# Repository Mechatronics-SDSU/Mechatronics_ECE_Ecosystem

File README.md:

# Mechatronics_ECE_Ecosystem
Center for anything that makes lights blink and motors spin.
  
The new revision of a cohesive electrical system to support all Mechatronics projects consisting of several "modules" communicating on shared multi-drop buses. 
Each module consists of:
- Hardware (schematic + PCB)
- Firmware and Build Files
- Fabrication files
  
Each module shall:
- Have a specific and well scoped goal
- Serve to more efficiently distribute processing as a part of the whole system
- Respect the shared communications standards defined in this repository
- Be well researched, tested, and documented

## Repository Structure
- Embedded CAN Bus
    - Contains documentation and libraries for inter-module communications

- Board Support
    - List of supported hardware
    - Contains information on supported MCU/FPGAs
    - Example projects and guides on how to use and implement a specific device

- General Documentation
    - well... it's in the name
    - Overall architectural goals and descriptions of our target system and all current/future needs

- KiCad Libraries
    - KiCad 7 symbols, footprints, and models created for individual modules

## General Hardware Support
A set of selected processors and FPGAs are listed that contain the requisite information to quickly bring any project up. These parts are by no means the only acceptable options, but are provided to reduce the load when starting a project.

Also run linux, it makes all of this so much easier. :)

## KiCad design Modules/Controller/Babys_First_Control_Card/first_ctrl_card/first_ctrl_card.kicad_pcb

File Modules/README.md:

# Modules
Several modules are required to sustain an effective system.  
A module may be standalone, or represent a subsystem that requires a single point of bus interface (notably Power System Management).
  
To better organize the multiple projects that will be present here another layer of directories are present.
### Acoustics and Communication
- Hydrophone direction finding
- Acoustic data processing / collection
- Optical and Acoustic Communications methods
### Controller
- Main bus controller
- Interface with embedded computers (Jetsons, Pis, etc..)
### Human Interface
- Controls boxes
- Lighting systems
### Motion
- ESC Drivers
- Servo Controllers
- Motion Processing
### Power Systm
- Power conversion (DC-DC, AC-DC)
- Power monitoring
- Battery priority and failover
- Battery charging
- Power path management
### Safety
- Internal system state
- Temperature and leak monitoring
- General system watchdog
### Example
- Template Project

## Completed Modules
  
## Modules In Progress
- Bus Manager / Computer Interface Module
- Human Interface Module
- System Health Monitoring Module
- Motor and Drive Control Module
- RGB Pattern Module
- Power System Management
- Hydrophone Direction Finding
- Acoustic Communications
- A ton of power projects

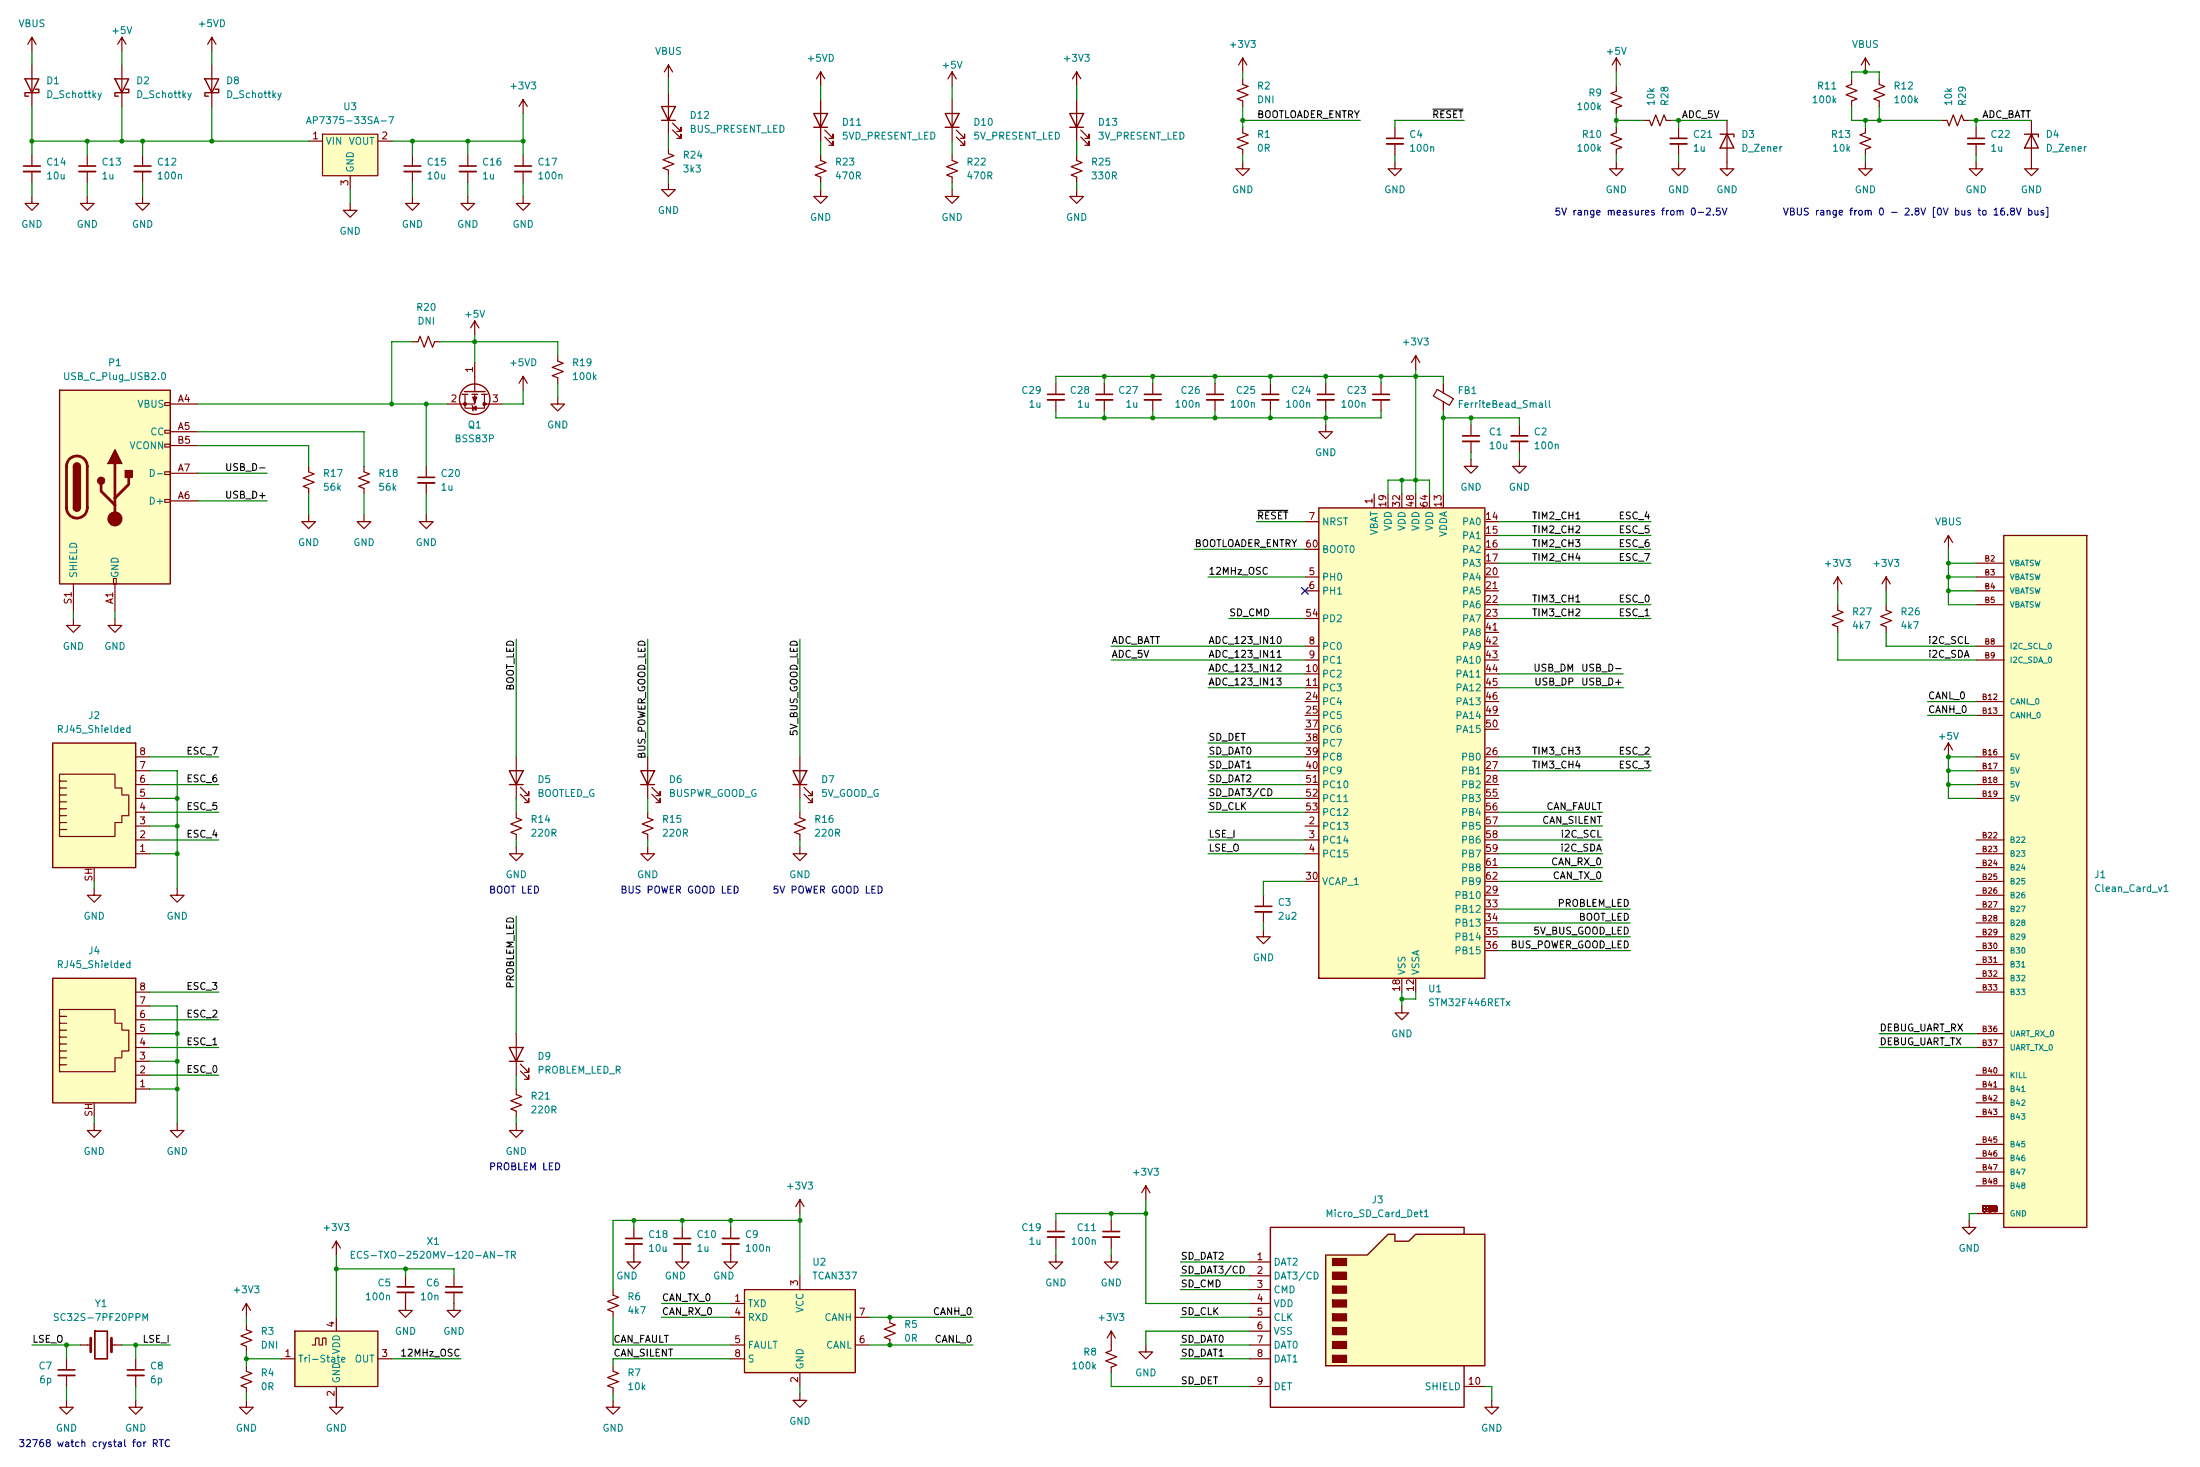
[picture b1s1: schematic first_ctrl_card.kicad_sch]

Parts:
C1, C14, C15, C18: 10u; C_0805_2012Metric
C2, C4, C5, C9, C11, C12, C17, C23, C24, C25, C26: 100n; C_0805_2012Metric
C3: 2u2; C_0805_2012Metric
C6: 10n; C_0805_2012Metric
C7, C8: 6p; C_0805_2012Metric
C10, C13, C16, C19, C20, C21, C22, C27, C28, C29: 1u; C_0805_2012Metric
D1, D2, D8: D_Schottky; D_SOD-123
D3, D4: D_Zener; D_SOD-123
D5: BOOTLED_G; LED_0805_2012Metric
D6: BUSPWR_GOOD_G; LED_0805_2012Metric
D7: 5V_GOOD_G; LED_0805_2012Metric
D9: PROBLEM_LED_R; LED_0805_2012Metric
D10: 5V_PRESENT_LED; LED_0805_2012Metric
D11: 5VD_PRESENT_LED; LED_0805_2012Metric
D12: BUS_PRESENT_LED; LED_0805_2012Metric
D13: 3V_PRESENT_LED; LED_0805_2012Metric
FB1: FerriteBead_Small; L_0603_1608Metric
J1: Clean_Card_v1; official_mechatronics_card; PARTREV S
J2, J4: RJ45_Shielded; RJ45_Ninigi_GE
J3: Micro_SD_Card_Det1; MSD-1-A_SD_CARD_W_DET
P1: USB_C_Plug_USB2.0; USB_C_Receptacle_GCT_USB4105-xx-A_16P_TopMnt_Horizontal
Q1: BSS83P; SOT-23
R1, R4, R5: 0R; R_0805_2012Metric
R2, R3, R20: DNI; R_0805_2012Metric
R6, R26, R27: 4k7; R_0805_2012Metric
R7, R13, R28, R29: 10k; R_0805_2012Metric
R8, R9, R10, R11, R12, R19: 100k; R_0805_2012Metric
R14, R15, R16, R21: 220R; R_0805_2012Metric
R17, R18: 56k; R_0805_2012Metric
R22, R23: 470R; R_0805_2012Metric
R24: 3k3; R_0805_2012Metric
R25: 330R; R_0805_2012Metric
U1: STM32F446RETx; LQFP-64_10x10mm_P0.5mm
U2: TCAN337; TSOT-23-8
U3: AP7375-33SA-7; SOT-23-3
X1: ECS-TXO-2520MV-120-AN-TR; Oscillator_SMD_ECS_2520MV-xxx-xx-4Pin_2.5x2.0mm
Y1: SC32S-7PF20PPM

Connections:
+3V3: C5.1, C6.1, C9.1, C10.1, C11.1, C15.1, C16.1, C17.1, C18.1, C19.1, C23.1, C24.1, C25.1, C26.1, C27.1, C28.1, C29.1, D13.2 (A), FB1.2, J3.4 (VDD), R2.1, R3.1, R6.1, R8.1, R26.1, R27.1, U1.19 (VDD), U1.32 (VDD), U1.48 (VDD), U1.64 (VDD), U2.3 (VCC), U3.2 (VOUT), X1.4 (VDD)
+5V: D2.2 (A), D10.2 (A), J1.B16 (5V), J1.B17 (5V), J1.B18 (5V), J1.B19 (5V), Q1.1 (G), R9.1, R19.1, R20.2
+5VD: D8.2 (A), D11.2 (A), Q1.3 (D)
/5V_BUS_GOOD_LED: D7.2 (A), U1.35 (PB14)
/12MHz_OSC: U1.5 (PH0), X1.3 (OUT)
/ADC_123_IN10: C22.1, D4.1 (K), R29.1, U1.8 (PC0)
/ADC_123_IN11: C21.1, D3.1 (K), R28.1, U1.9 (PC1)
/ADC_123_IN12: U1.10 (PC2)
/ADC_123_IN13: U1.11 (PC3)
/BOOTLOADER_ENTRY: R1.1, R2.2, U1.60 (BOOT0)
/BOOT_LED: D5.2 (A), U1.34 (PB13)
/BUS_POWER_GOOD_LED: D6.2 (A), U1.36 (PB15)
/CANH_0: J1.B13 (CANH_0), R5.1, U2.7 (CANH)
/CANL_0: J1.B12 (CANL_0), R5.2, U2.6 (CANL)
/CAN_FAULT: R6.2, U1.56 (PB4), U2.5 (FAULT)
/CAN_RX_0: U1.61 (PB8), U2.4 (RXD)
/CAN_SILENT: R7.1, U1.57 (PB5), U2.8 (S)
/CAN_TX_0: U1.62 (PB9), U2.1 (TXD)
/DEBUG_UART_RX: J1.B36 (UART_RX_0)
/DEBUG_UART_TX: J1.B37 (UART_TX_0)
/ESC_0: J4.2, U1.22 (PA6)
/ESC_1: J4.4, U1.23 (PA7)
/ESC_2: J4.6, U1.26 (PB0)
/ESC_3: J4.8, U1.27 (PB1)
/ESC_4: J2.2, U1.14 (PA0)
/ESC_5: J2.4, U1.15 (PA1)
/ESC_6: J2.6, U1.16 (PA2)
/ESC_7: J2.8, U1.17 (PA3)
/LSE_I: C8.1, U1.3 (PC14), Y1.2
/LSE_O: C7.1, U1.4 (PC15), Y1.1
/PROBLEM_LED: D9.2 (A), U1.33 (PB12)
/SD_CLK: J3.5 (CLK), U1.53 (PC12)
/SD_CMD: J3.3 (CMD), U1.54 (PD2)
/SD_DAT0: J3.7 (DAT0), U1.39 (PC8)
/SD_DAT1: J3.8 (DAT1), U1.40 (PC9)
/SD_DAT2: J3.1 (DAT2), U1.51 (PC10)
/SD_DAT3/CD: J3.2 (DAT3/CD), U1.52 (PC11)
/SD_DET: J3.9 (DET), R8.2, U1.38 (PC7)
/USB_D+: P1.A6 (D+), U1.45 (PA12)
/USB_D-: P1.A7 (D-), U1.44 (PA11)
/i2C_SCL: J1.B8 (I2C_SCL_0), R26.2, U1.58 (PB6)
/i2C_SDA: J1.B9 (I2C_SDA_0), R27.2, U1.59 (PB7)
/~RESET: C4.1, U1.7 (NRST)
GND: C1.2, C2.2, C3.2, C4.2, C5.2, C6.2, C7.2, C8.2, C9.2, C10.2, C11.2, C12.2, C13.2, C14.2, C15.2, C16.2, C17.2, C18.2, C19.2, C20.2, C21.2, C22.2, C23.2, C24.2, C25.2, C26.2, C27.2, C28.2, C29.2, D3.2 (A), D4.2 (A), J1.B1 (GND), J1.B6 (GND), J1.B7 (GND), J1.B10 (GND), J1.B11 (GND), J1.B14 (GND), J1.B15 (GND), J1.B20 (GND), J1.B21 (GND), J1.B34 (GND), J1.B35 (GND), J1.B38 (GND), J1.B39 (GND), J1.B44 (GND), J1.B49 (GND), J2.1, J2.3, J2.5, J2.7, J2.SH, J3.6 (VSS), J3.10 (SHIELD), J4.1, J4.3, J4.5, J4.7, J4.SH, P1.A1 (GND), P1.A12 (GND), P1.B1 (GND), P1.B12 (GND), P1.S1 (SHIELD), R1.2, R4.2, R7.2, R10.2, R13.2, R14.2, R15.2, R16.2, R17.2, R18.2, R19.2, R21.2, R22.2, R23.2, R24.2, R25.2, U1.12 (VSSA), U1.18 (VSS), U1.31 (VSS), U1.47 (VSS), U1.63 (VSS), U2.2 (GND), U3.3 (GND), X1.2 (GND)
unnamed: C12.1, C13.1, C14.1, D1.1 (K), D2.1 (K), D8.1 (K), U3.1 (VIN)
unnamed: D5.1 (K), R14.1
unnamed: D6.1 (K), R15.1
unnamed: D7.1 (K), R16.1
unnamed: D9.1 (K), R21.1
unnamed: D10.1 (K), R22.1
unnamed: D11.1 (K), R23.1
unnamed: D12.1 (K), R24.1
unnamed: D13.1 (K), R25.1
unnamed: P1.A5 (CC), R18.1
unnamed: P1.B5 (VCONN), R17.1
unnamed: C20.1, P1.A4 (VBUS), P1.A9 (VBUS), P1.B4 (VBUS), P1.B9 (VBUS), Q1.2 (S), R20.1
unnamed: R9.2, R10.1, R28.2
unnamed: R11.2, R12.2, R13.1, R29.2
unnamed: C3.1, U1.30 (VCAP_1)
unnamed: C1.1, C2.1, FB1.1, U1.13 (VDDA)
unnamed: R3.2, R4.1, X1.1 (Tri-State)
VBUS: D1.2 (A), D12.2 (A), J1.B2 (VBATSW), J1.B3 (VBATSW), J1.B4 (VBATSW), J1.B5 (VBATSW), R11.1, R12.1

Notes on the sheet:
PROBLEM LED
VBUS range from 0 - 2.8V [0V bus to 16.8V bus]
5V POWER GOOD LED
BUS POWER GOOD LED
BOOT LED
5V range measures from 0-2.5V
32768 watch crystal for RTC

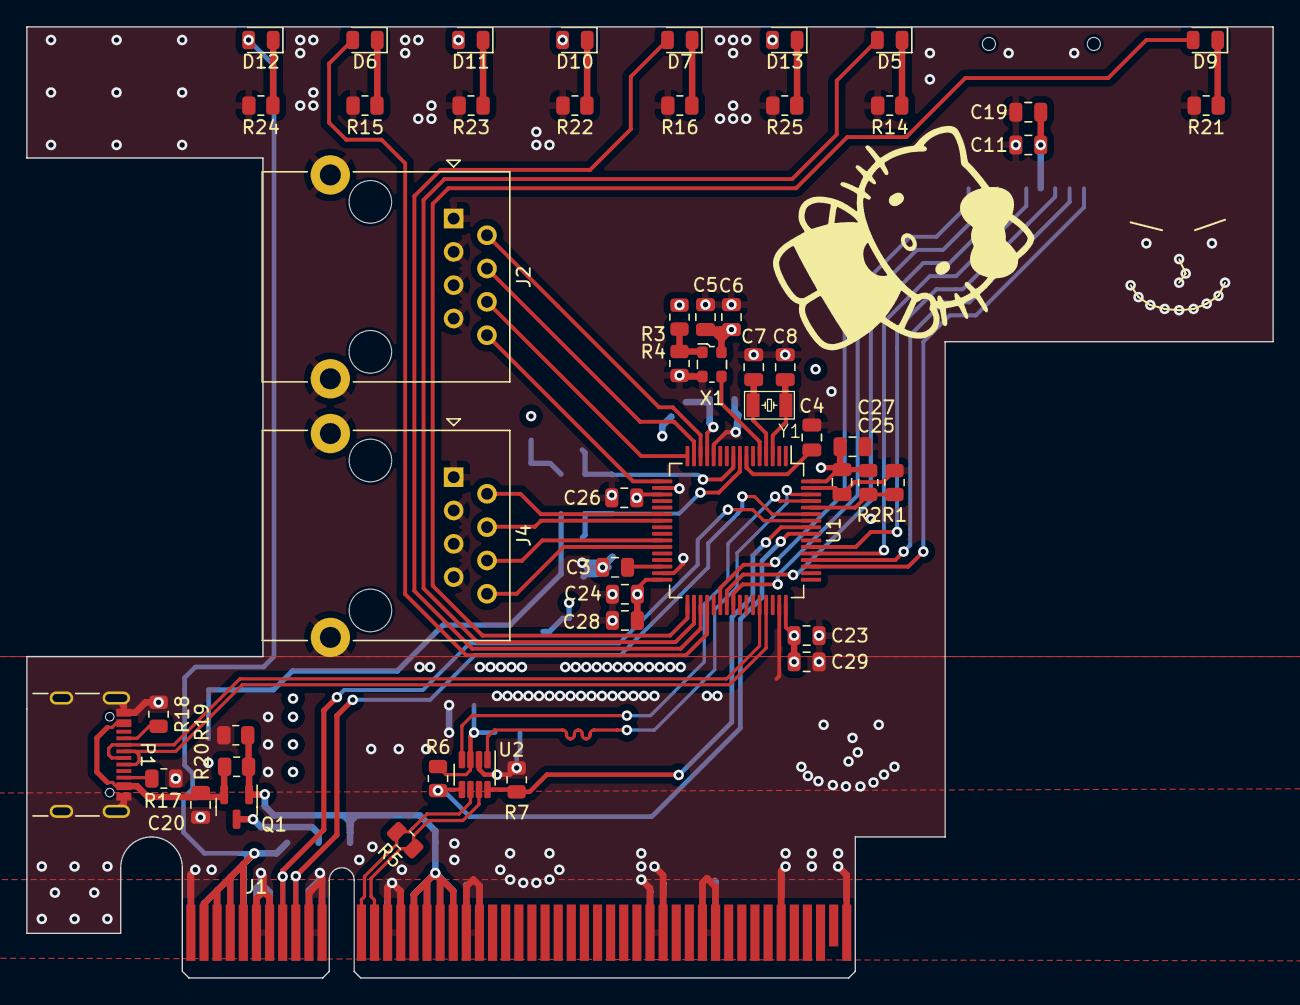
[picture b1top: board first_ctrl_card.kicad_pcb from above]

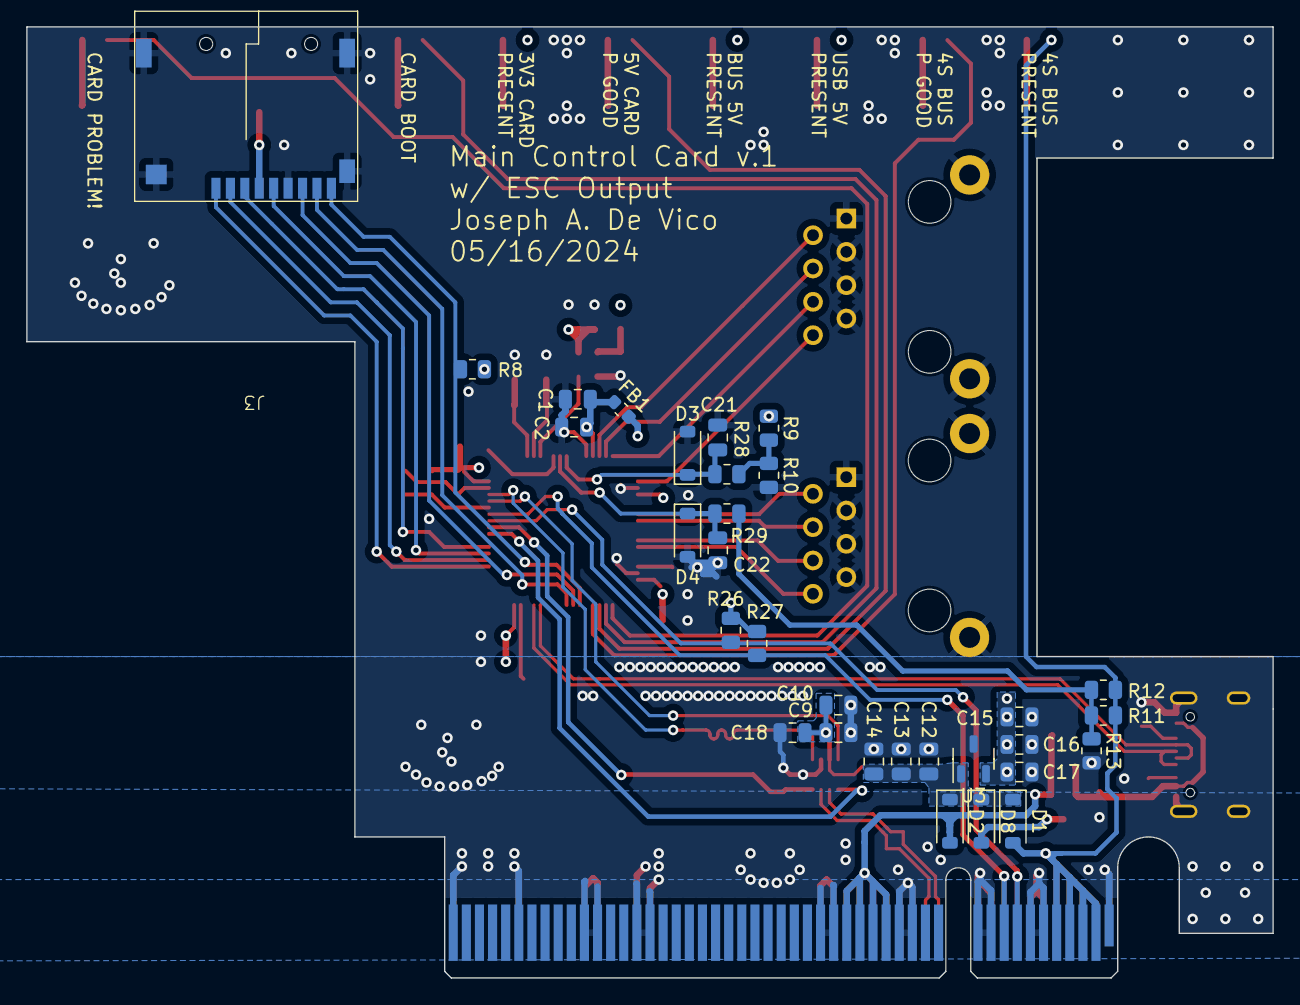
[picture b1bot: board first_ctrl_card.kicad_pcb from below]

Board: 4 copper layers, 95.0 x 72.5 mm, 83 parts (31 on the bottom side), 58 nets.

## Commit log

2024-02-11 RP2040 guide added
2024-04-20 This is not a virus I swear to got please ACCEPT THIS COMMIT IT WILL NOT GIVE YOU RANSOMWEAR THAT WILL COST 15,000 iranian Rial to my Monero Wallet at 0x80019ab0. OK THANK YOU FOR ACCEPRING MY COMMIT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
2024-04-27 This is wa good one Trust bro
2024-04-27 Wee woo example added
2024-04-27 Almost done with card profile
2024-05-10 Control card dump
2024-05-10 Fixed
2024-05-23 BCU Folder addition Will V0
2024-05-23 Fixed windows file endings
2024-05-23 Testing
2024-05-23 Jon Commit Test
